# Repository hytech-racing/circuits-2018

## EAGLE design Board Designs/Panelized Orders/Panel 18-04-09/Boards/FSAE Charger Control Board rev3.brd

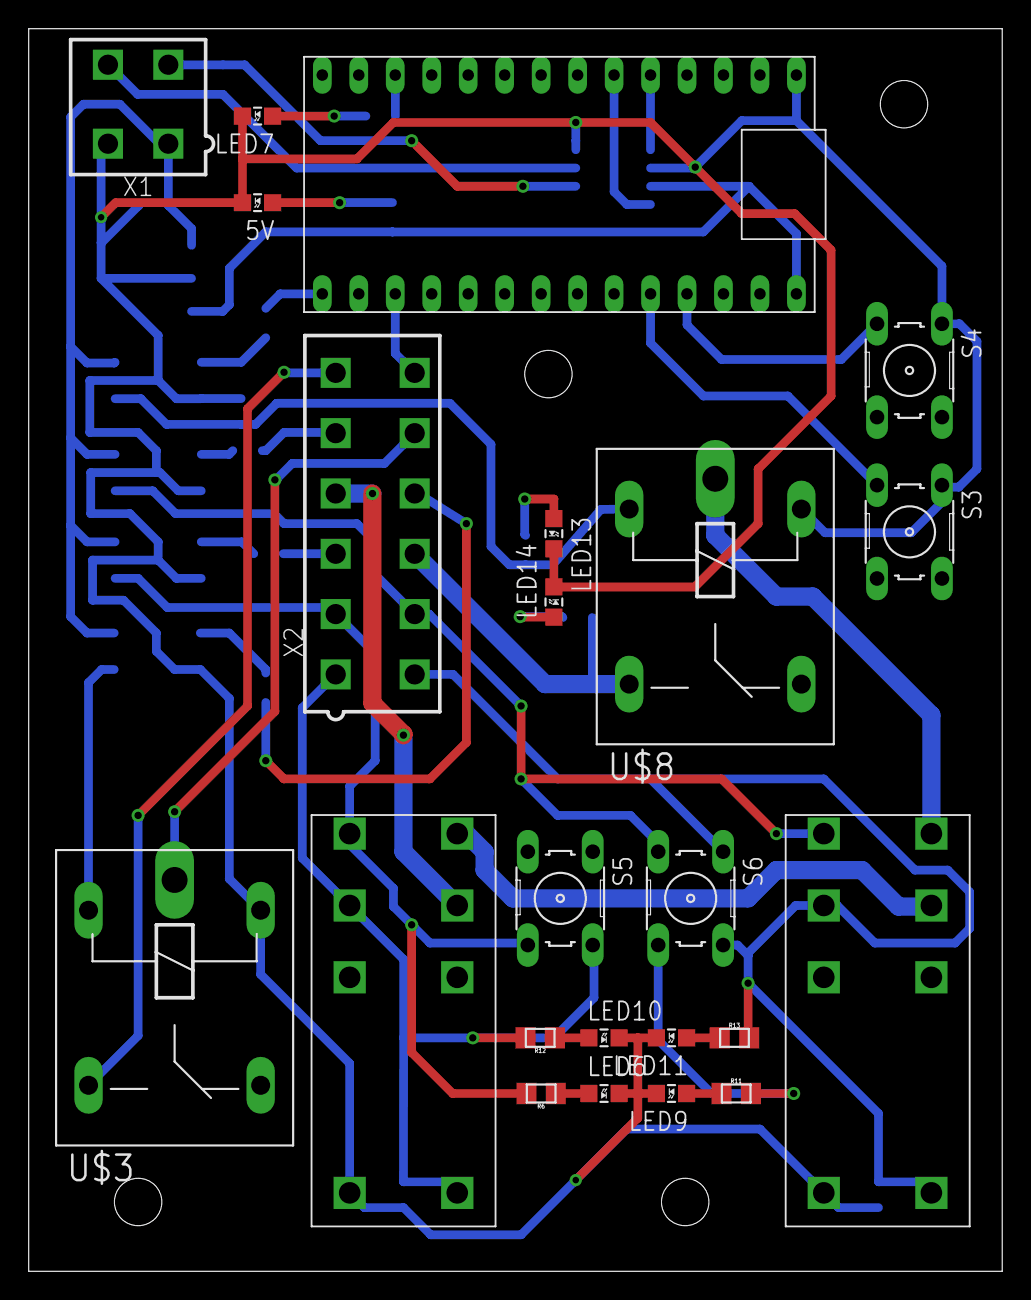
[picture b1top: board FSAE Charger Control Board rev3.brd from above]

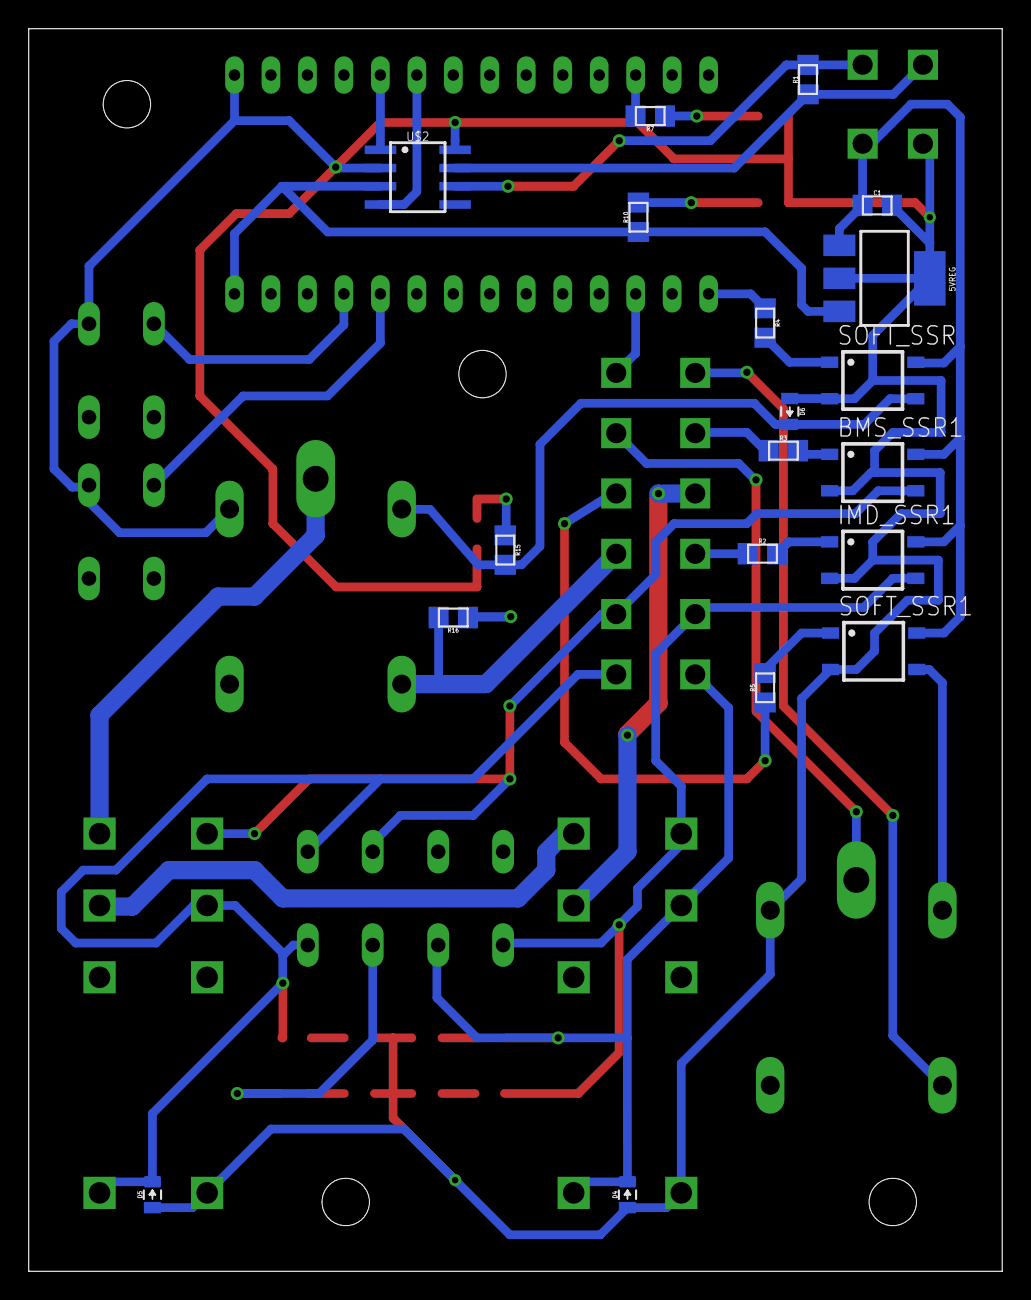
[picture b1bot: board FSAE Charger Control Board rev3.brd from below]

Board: 2 copper layers, 67.8 x 86.5 mm, 42 parts (19 on the bottom side), 39 nets.

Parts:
5V: LED-805
5VREG: SOT223
BMS_SSR1: CPC1002N; SOP04
C1: .22uF; 0805
D4, D5, D6: DIODE0805; 0805_D
IMD_SSR1: CPC1002N; SOP04
LED6, LED7, LED9, LED10, LED11, LED13, LED14: LED-805
R1: 120; 0805
R2, R3, R4, R5, R6, R7, R10, R11, R12, R13, R15, R16: 0805
S3, S4, S5, S6: B3F-10XX
SOFT_SSR, SOFT_SSR1: CPC1002N; SOP04
U$1: TEENSY_3.2_SIMPLE
U$2: MCP2551; SOIC-08
U$3, U$8: G5LE; ZF112
U$6, U$7: G2RL-2-DC12; G2RL-2
X1: CONNECTOR-4; MINIFIT_5566-4
X2: CONNECTOR-12; MINIFIT_5566-12

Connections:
+5V: 5VREG.3, R10.1, U$1.VIN, U$2.3
+12V: 5VREG.1, BMS_SSR1.4, C1.1, IMD_SSR1.4, SOFT_SSR.4, SOFT_SSR1.4, X1.1
BMS_12V: BMS_SSR1.3, R11.2, S6.3, S6.4, U$7.4, X2.8
BMS_INRLK: R5.1, X2.10
BMS_OK: D5.C, R13.2, S6.1, S6.2, U$7.3, U$7.COIL-, X2.7
BTN_X: S4.3, U$1.A9
BTN_Y: S3.3, U$1.A8
CANH: R1.1, U$2.7, X1.4
CANL: R1.2, U$2.6, X1.3
CANRX: U$1.D4(CANRX), U$2.4
CANTX: U$1.D3(CANTX), U$2.1
GND: 5V.C, 5VREG.2, 5VREG.4, BMS_SSR1.2, C1.2, D4.A, D5.A, D6.A, IMD_SSR1.2, LED6.C, LED7.C, LED9.C, LED10.C, LED11.C, LED13.C, LED14.C, S3.1, S4.1, SOFT_SSR.2, SOFT_SSR1.2, U$1.GND, U$2.2, U$2.8, U$3.1, U$6.COIL+, U$7.COIL+, U$8.1, X1.2
GPIO: U$1.A1, X2.12
IMD_12V: IMD_SSR1.3, R6.2, S5.3, S5.4, U$6.4, X2.2
IMD_OK: D4.C, R12.2, S5.1, S5.2, U$6.3, U$6.COIL-, X2.1
unnamed: SOFT_SSR1.3, U$3.2
unnamed: LED7.A, R7.1
unnamed: 5V.A, R10.2
unnamed: IMD_SSR1.1, R2.2
unnamed: U$3.S, X2.6
unnamed: LED6.A, R6.1
unnamed: LED9.A, R11.1
unnamed: LED10.A, R12.1
unnamed: U$3.P, X2.11
unnamed: R7.2, U$1.D10(TX2)
unnamed: BMS_SSR1.1, R3.2
unnamed: LED11.A, R13.1
unnamed: LED14.A, R16.1
unnamed: LED13.A, R15.1
unnamed: R2.1, X2.3
unnamed: R3.1, X2.5
unnamed: R5.2, SOFT_SSR1.1
unnamed: R4.1, U$1.D13
SHUTDOWN_IN: U$6.6, X2.4
SHUTDOWN_IN_A: U$6.5, U$7.6
SHUTDOWN_IN_B: U$7.5, U$8.P
SHUTDOWN_OUT: R16.2, U$8.S, X2.9
SW_KILL: R4.2, SOFT_SSR.1
SW_KILL_RELAY: D6.C, R15.2, SOFT_SSR.3, U$8.2

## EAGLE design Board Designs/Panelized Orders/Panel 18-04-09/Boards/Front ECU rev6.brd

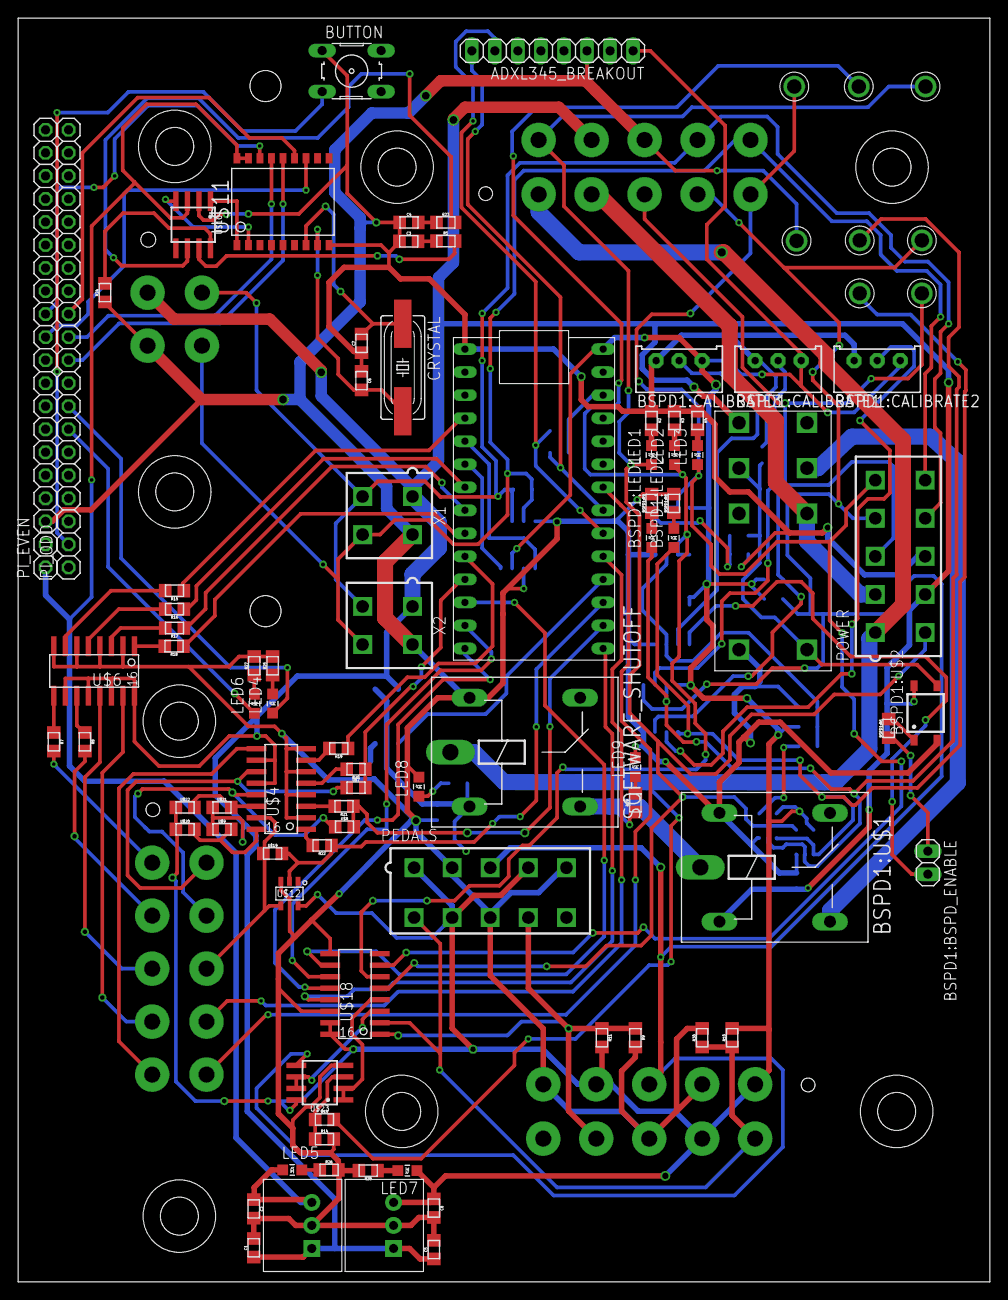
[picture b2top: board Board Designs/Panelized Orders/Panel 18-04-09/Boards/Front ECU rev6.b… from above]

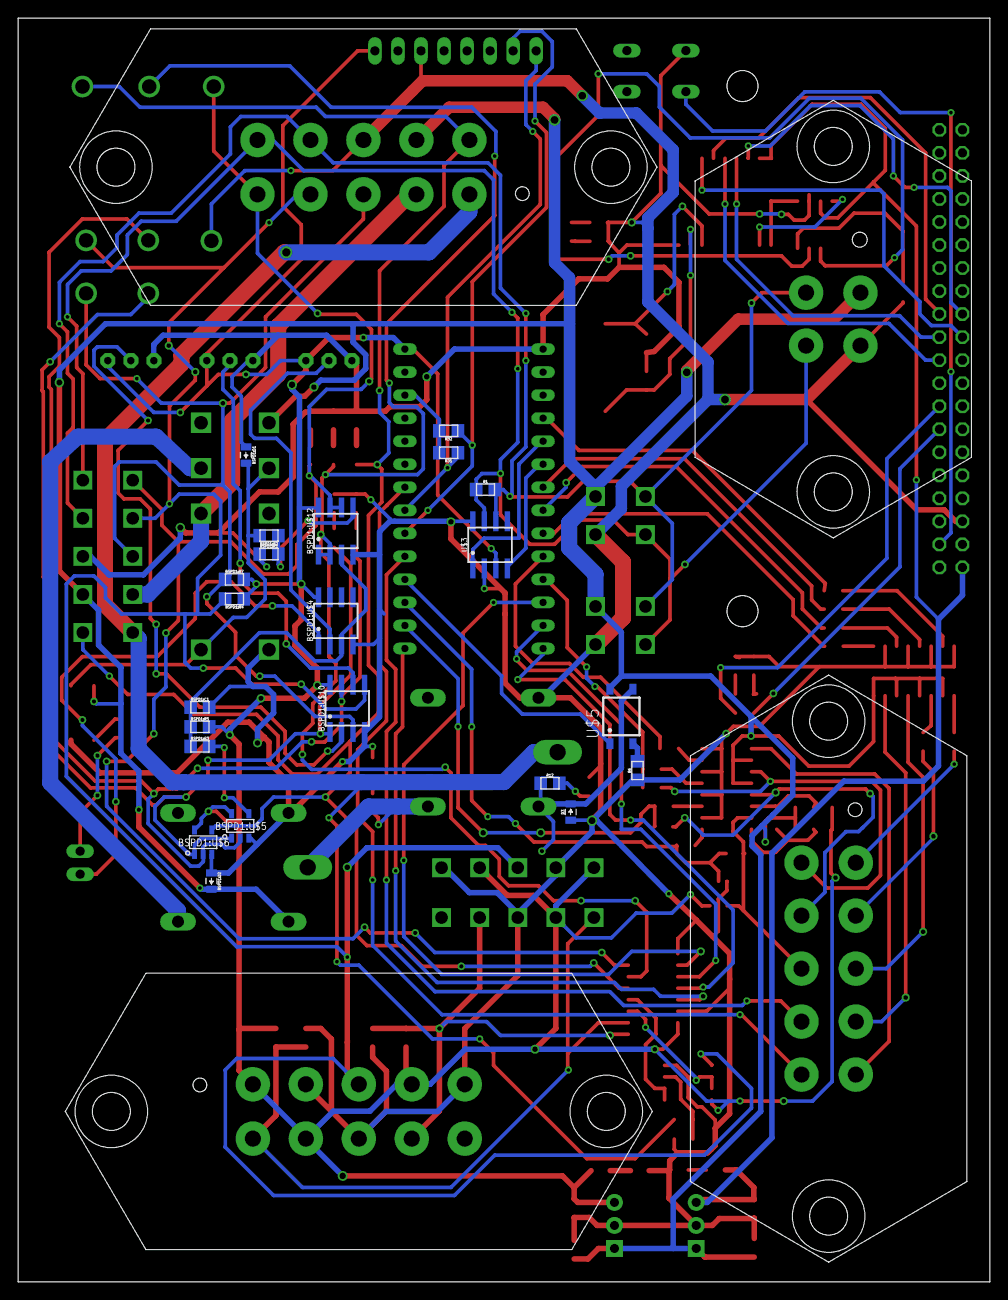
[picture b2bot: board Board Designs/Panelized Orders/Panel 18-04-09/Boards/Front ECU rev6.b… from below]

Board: 2 copper layers, 107.2 x 139.4 mm, 117 parts (26 on the bottom side), 102 nets.

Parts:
ADXL345_BREAKOUT: 1X08
BSPD1:BSPD_ENABLE: JUMPER; 1X02
BSPD1:C1: .47u; 0805
BSPD1:CALIBRATE1, BSPD1:CALIBRATE2, BSPD1:CALIBRATE3: TRIMPOT_3296
BSPD1:D1, BSPD1:D2: DIODE0805; 0805_D
BSPD1:LED1: RED; LED-805
BSPD1:LED2: YELLOW; LED-805
BSPD1:R1: 12k; 0805
BSPD1:R2: 43k; 0805
BSPD1:R3: 330; 0805
BSPD1:R4, BSPD1:R7: 10k; 0805
BSPD1:R5: 680k; 0805
BSPD1:R6: 680; 0805
BSPD1:R8, BSPD1:R9: 270; 0805
BSPD1:U$1: G5LE; ZF112
BSPD1:U$2: CPC1002N; SOP04
BSPD1:U$3: JW2SN-DC12V; JW2SN
BSPD1:U$4, BSPD1:U$10: MCP6542SOIC; SOIC-08
BSPD1:U$5: SN74AHC1G09; SOT-23-5
BSPD1:U$6: SN74LVC1G08; SOT-23-5
BSPD1:U$11, BSPD1:U$13: TEST_POINT
BSPD1:U$12: MCP6002SOIC; SOIC-08
BUTTON: B3F-10XX
C1, C2, C5, C8: 10uF; 0805
C3, C4: 560pF; 0805
C6, C7: 22pF; 0805
CRYSTAL: 16MHz; HC49UP
D3: DIODE0805; 0805_D
IC2, IC3: OKI-78SR
LED1, LED6, LED8, LED9: RED; LED-805
LED2: YELLOW; LED-805
LED3, LED4: GREEN; LED-805
LED5, LED7: PURPLE; LED-805
PEDALS: MINIFIT_5566-10
PI_EVEN: 1X20
PI_ODD: 1X20
POWER: MINIFIT_5566-10
R1: 120; 0805
R2, R3, R15, R16, R17, R18, R19, R20, R21, R22, R27: 270; 0805
R4, R25, R26, R28: 200; 0805
R5, R23: 100; 0805
R6: 330; 0805
R7, R8: 0; 0805
R9, R10, R11, R30: 10k; 0805
R12, R29: 1.2K; 0805
R13: 43k; 0805
R14: 12k; 0805
R24, R31, R32: 4.7k; 0805
SOFTWARE_SHUTOFF: G5LE; ZF112
U$1: TEENSY_3.2_SIMPLE
U$2, U$13, U$14, U$15, U$16, U$17: TEST_POINT
U$3, U$10: MCP2551; SOIC-08
U$4, U$6: TLP291-4; SOIC-16
U$5: CPC1002N; SOP04
U$7, U$8, U$9, U$19, U$20, U$21, U$22: JUMPER; 0805
U$11: MCP2515SMD; SOIC-18W
U$12: SN74LV1T34; SOT-23-5
U$18: MCP3208SOIC; SOIC-16
U$23: MCP6002SOIC; SOIC-08
X1, X2: CONNECTOR-4; MINIFIT_5566-4
X3: CONNECTOR-4MX150L_VERTICAL-4; MX150L_VERTICAL-4
X4, X5, X6: CONNECTOR-10MX150L_VERTICAL-10; MX150L_VERTICAL-10

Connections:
3.3V+: R31.2, R32.2, U$1.3.3V
+5V: ADXL345_BREAKOUT.1, BSPD1:CALIBRATE1.1, BSPD1:CALIBRATE2.1, BSPD1:CALIBRATE3.1, BSPD1:R4.1, BSPD1:R5.2, BSPD1:R7.2, BSPD1:U$4.8, BSPD1:U$5.5, BSPD1:U$6.5, BSPD1:U$10.8, BSPD1:U$12.8, C8.1, IC3.3, LED7.A, PEDALS.1, PEDALS.4, PEDALS.7, R10.2, R11.2, U$1.VIN, U$3.3, U$12.5, U$18.15, U$18.16, U$20.1, U$22.1, U$23.8, X4.1, X4.4, X4.7
+5V/1: C2.1, IC2.3, LED5.A, PI_EVEN.1, U$10.3, U$11.17, U$11.18
+12V: BSPD1:D2.C, BSPD1:U$1.2, BSPD1:U$2.4, BSPD1:U$3.4, C1.1, C5.1, IC2.1, IC3.1, POWER.7, U$4.10, U$4.12, U$5.4, U$6.10, U$6.12, U$6.14, U$6.16, U$9.1, U$21.1, X1.1, X2.1, X3.1, X5.7
BSPD1:N$1: BSPD1:D1.C, BSPD1:R2.2, BSPD1:U$2.3, BSPD1:U$3.3, BSPD1:U$3.COIL-
BSPD1:N$2: BSPD1:R3.2, BSPD1:U$5.4
BSPD1:N$3: BSPD1:R6.2, BSPD1:U$2.1
BSPD1:N$4: BSPD1:BSPD_ENABLE.1, BSPD1:R6.1
BSPD1:N$5: BSPD1:CALIBRATE2.2, BSPD1:U$10.2
BSPD1:N$6: BSPD1:CALIBRATE1.2, BSPD1:U$10.6
BSPD1:N$7: BSPD1:CALIBRATE3.2, BSPD1:U$4.2
BSPD1:N$8: BSPD1:BSPD_ENABLE.2, BSPD1:U$4.1
BSPD1:N$9: BSPD1:R1.2, BSPD1:R2.1, BSPD1:U$12.5
BSPD1:N$13: BSPD1:C1.1, BSPD1:R3.1, BSPD1:R5.1, BSPD1:U$4.3, BSPD1:U$12.3
BSPD1:N$14: BSPD1:LED2.C, BSPD1:R8.1
BSPD1:N$15: BSPD1:LED1.C, BSPD1:R9.1
BSPD1:N$16: BSPD1:LED1.A, BSPD1:U$5.2, BSPD1:U$6.2, BSPD1:U$10.7, BSPD1:U$11.P$1
BSPD1:N$17: BSPD1:LED2.A, BSPD1:U$5.1, BSPD1:U$6.1, BSPD1:U$10.1, BSPD1:U$13.P$1
BSPD1:SHUTDOWN_C: BSPD1:U$1.S, BSPD1:U$3.6
BUT: BUTTON.3, PI_ODD.2
CAN-H: R5.2, U$10.7
CAN-L: R23.2, U$10.6
CANH: POWER.10, R1.1, U$3.7, X1.4, X2.4, X3.4, X5.10
CANL: POWER.9, R1.2, U$3.6, X1.3, X2.3, X3.3, X5.9
CS: PI_EVEN.12, U$11.16
CS_MCP3208: U$1.D10(TX2), U$18.10
DASH_CTRL1: R15.1, U$1.D2
DASH_CTRL2: R16.1, U$1.D5
DASH_CTRL3: R17.1, U$1.D6
DASH_CTRL4: R18.1, U$1.D7(RX3)
DASH_CTRL5: R19.1, U$1.D8(TX3)
DASH_CTRL6: R20.1, U$1.D9(RX2), U$7.2
DASH_CTRL7: R21.1, U$1.A0, U$8.2
DASH_CTRL8: R22.1, U$1.A1, U$12.2, U$19.2
DASH_CTRL9: U$1.A3, X6.9
DASH_CTRL10: U$1.A6, X6.10
DASH_IO1: R7.2, X6.1
DASH_IO2: R8.2, X6.2
DASH_IO3: U$6.13, X6.3
DASH_IO4: U$6.15, X6.4
DASH_IO5: U$4.9, X6.5
DASH_IO6: U$4.11, U$7.1, X6.6
DASH_IO7: U$4.13, U$8.1, X6.7
DASH_IO8: U$4.15, U$12.4, U$19.1, X6.8
GND: ADXL345_BREAKOUT.3, BSPD1:C1.2, BSPD1:CALIBRATE1.3, BSPD1:CALIBRATE2.3, BSPD1:CALIBRATE3.3, BSPD1:D1.A, BSPD1:D2.A, BSPD1:R1.1, BSPD1:R8.2, BSPD1:R9.2, BSPD1:U$1.1, BSPD1:U$2.2, BSPD1:U$3.COIL+, BSPD1:U$4.4, BSPD1:U$5.3, BSPD1:U$6.3, BSPD1:U$10.4, BSPD1:U$12.4, BUTTON.1, C1.2, C2.2, C3.1, C4.1, C5.2, C6.1, C7.1, C8.2, D3.A, IC2.2, IC3.2, LED8.C, LED9.C, PEDALS.2, PEDALS.5, PEDALS.8, PI_EVEN.3, POWER.8, R2.1, R3.1, R4.1, R6.1, R9.2, R14.2, R24.1, R25.2, R26.2, R27.2, R28.2, R30.2, SOFTWARE_SHUTOFF.1, U$1.GND, U$2.P$1, U$3.2, U$3.8, U$4.2, U$4.4, U$4.6, U$4.8, U$6.2, U$6.4, U$6.6, U$6.8, U$10.2, U$11.9, U$12.3, U$18.9, U$18.14, U$23.4, X1.2, X2.2, X3.2, X4.2, X4.5, X4.8, X5.8
INT: PI_EVEN.11, U$11.12
LED1: LED4.A, PI_ODD.8
LED2: LED6.A, PI_ODD.7
MISO: PI_ODD.11, U$11.15
MISO_TEENSY: U$1.D12, U$18.12
MOSI: PI_ODD.10, U$11.14
MOSI_TEENSY: U$1.D11, U$18.11
unnamed: R7.1, U$6.9
unnamed: U$1.D4(CANRX), U$3.4
unnamed: R8.1, U$6.11
unnamed: U$4.16, U$9.2, U$20.2
unnamed: U$1.D3(CANTX), U$3.1
unnamed: U$4.14, U$21.2, U$22.2
unnamed: R13.1, R14.1, U$23.3
unnamed: LED8.A, R12.2
unnamed: LED9.A, R29.2
unnamed: D3.C, R12.1, SOFTWARE_SHUTOFF.2, U$5.3
unnamed: LED1.C, R2.2
unnamed: LED2.C, R3.2
unnamed: LED3.C, R4.2
unnamed: R15.2, U$6.7
unnamed: R6.2, U$5.2
unnamed: R16.2, U$6.5
unnamed: R21.2, U$4.3
unnamed: R17.2, U$6.3
unnamed: R18.2, U$6.1
unnamed: R19.2, U$4.7
unnamed: R20.2, U$4.5
unnamed: R22.2, U$4.1
unnamed: U$10.1, U$11.1
unnamed: U$10.4, U$11.2
unnamed: C6.2, CRYSTAL.2, U$11.8
unnamed: R24.2, U$10.8
unnamed: C7.2, CRYSTAL.1, U$11.7
unnamed: C3.2, R5.1
unnamed: C4.2, R23.1
unnamed: LED4.C, R25.1
unnamed: LED5.C, R26.1
unnamed: LED6.C, R27.1
unnamed: LED7.C, R28.1
READ_BRAKE: U$18.3, U$23.6, U$23.7
READ_CHARGE: BSPD1:U$12.1, BSPD1:U$12.2, LED2.A, U$16.P$1, U$18.6
READ_FAULT: BSPD1:U$12.6, BSPD1:U$12.7, LED3.A, POWER.5, U$15.P$1, U$18.7, X5.5
READ_SWITCH: BSPD1:U$6.4, LED1.A, POWER.6, U$17.P$1, U$18.5, X5.6
READ_UPSTREAM_SHUTDOWN: U$18.4, U$23.1, U$23.2
SCK: PI_ODD.12, U$11.13
SCK_TEENSY: U$1.D13, U$18.13
SCL: ADXL345_BREAKOUT.8, R31.1, U$1.A5
SDA: ADXL345_BREAKOUT.7, R32.1, U$1.A4
SHUTDOWN_A: POWER.1, R13.2, SOFTWARE_SHUTOFF.P, X5.1
SHUTDOWN_B: BSPD1:U$1.P, R29.1, SOFTWARE_SHUTOFF.S
SHUTDOWN_D: BSPD1:U$3.7, POWER.2, X5.2
SHUTDOWN_RELAY_CTRL: U$1.A2, U$5.1
SIGNAL_ACCEL1: PEDALS.9, R9.1, R11.1, U$18.1, X4.9
SIGNAL_ACCEL2: PEDALS.6, R10.1, R30.1, U$18.2, X4.6
SIGNAL_BRAKE: BSPD1:R4.2, BSPD1:U$10.5, PEDALS.3, POWER.4, U$13.P$1, U$23.5, X4.3, X5.4
SIGNAL_CURRENT: BSPD1:R7.1, BSPD1:U$10.3, POWER.3, U$14.P$1, X5.3

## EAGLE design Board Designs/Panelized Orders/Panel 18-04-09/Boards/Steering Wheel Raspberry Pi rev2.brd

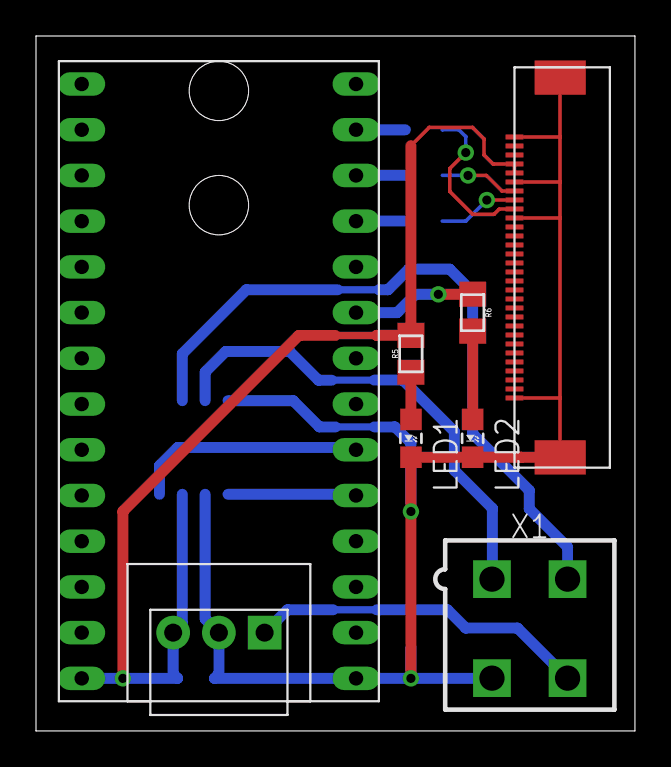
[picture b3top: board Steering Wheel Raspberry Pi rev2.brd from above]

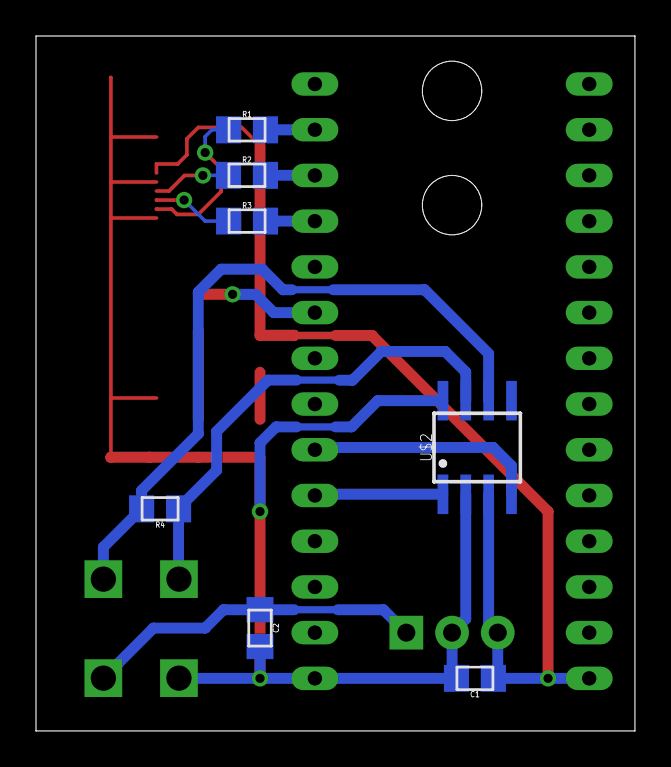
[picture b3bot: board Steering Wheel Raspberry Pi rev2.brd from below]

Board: 2 copper layers, 33.3 x 38.6 mm, 15 parts (7 on the bottom side), 16 nets.

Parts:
C1: 0.1uF; 0805
C2: 0.33uF; 0805
IC1: TO-220
LED1, LED2: LED-805
R1, R2, R3, R5, R6: 0805
R4: 120; 0805
U$1: TEENSY_3.2_SIMPLE
U$2: MCP2551; SOIC-08
U$3: FFC-30P-0.5MM
X1: CONNECTOR-4; MINIFIT_5566-4

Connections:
+5V: C1.1, IC1.3, R5.2, U$1.VIN, U$2.3, U$3.26, U$3.27
+12V: C2.1, IC1.1, X1.4
CANH: R4.1, U$2.7, X1.1
CANL: R4.2, U$2.6, X1.2
CANRX: U$1.D4(CANRX), U$2.4
CANTX: U$1.D3(CANTX), U$2.1
GND: C1.2, C2.2, IC1.2, LED1.C, LED2.C, U$1.GND, U$2.2, U$2.8, U$3.1, U$3.21, U$3.25, U$3.30, U$3.PAD@0, U$3.PAD@1, X1.3
unnamed: LED1.A, R5.1
unnamed: R6.1, U$1.D7(RX3)
unnamed: LED2.A, R6.2
RESET: R1.1, U$3.22
RX0: R3.1, U$3.23
TX0: R2.1, U$3.24
UC_RST: R1.2, U$1.D11
UC_RX: R3.2, U$1.D9(RX2)
UC_TX: R2.2, U$1.D10(TX2)

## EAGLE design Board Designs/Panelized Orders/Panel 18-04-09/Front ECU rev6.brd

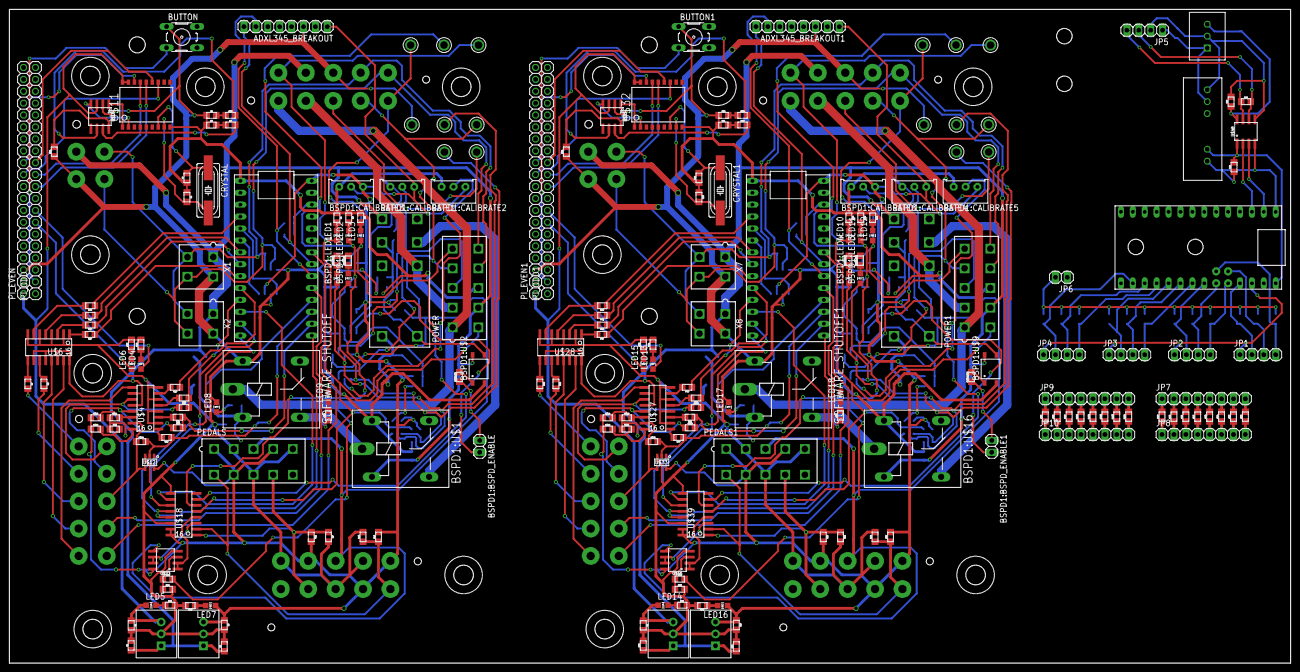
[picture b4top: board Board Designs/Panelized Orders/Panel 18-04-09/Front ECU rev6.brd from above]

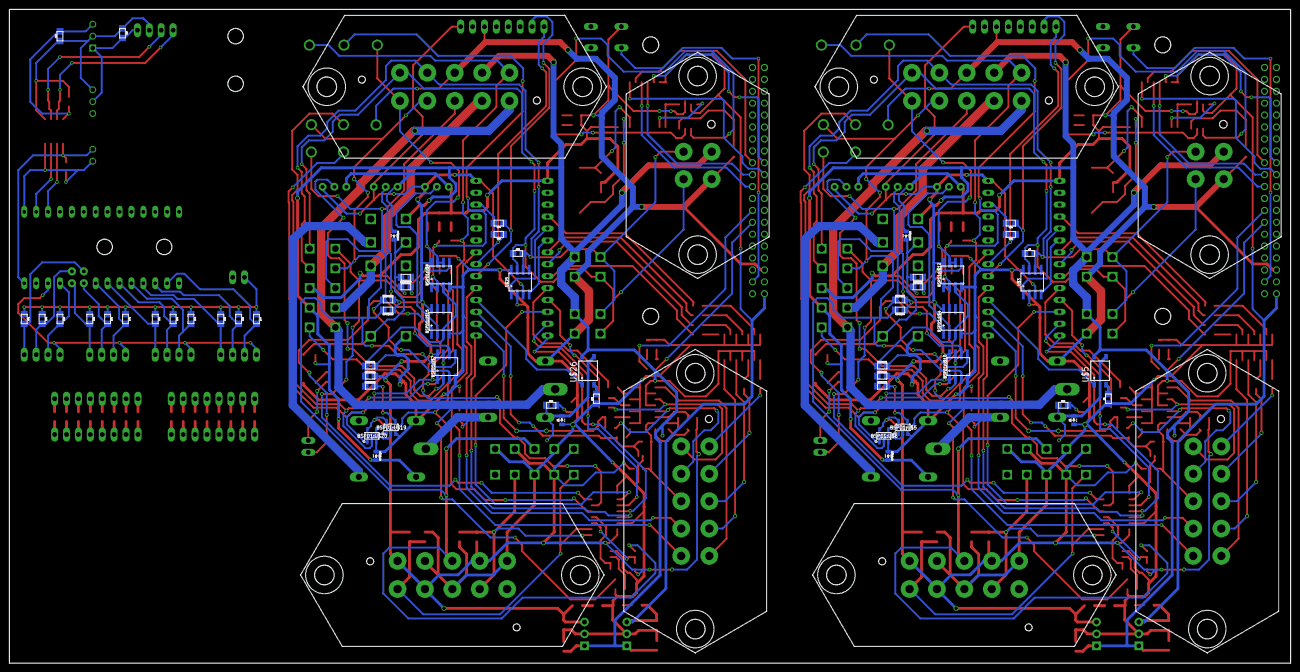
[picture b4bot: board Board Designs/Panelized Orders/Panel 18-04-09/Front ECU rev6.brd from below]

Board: 2 copper layers, 273.3 x 139.4 mm, 281 parts (66 on the bottom side), 259 nets.

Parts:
ADXL345_BREAKOUT, ADXL345_BREAKOUT1: 1X08
BSPD1:BSPD_ENABLE, BSPD1:BSPD_ENABLE1: JUMPER; 1X02
BSPD1:C1, BSPD1:C2: .47u; 0805
BSPD1:CALIBRATE1, BSPD1:CALIBRATE2, BSPD1:CALIBRATE3, BSPD1:CALIBRATE4, BSPD1:CALIBRATE5, BSPD1:CALIBRATE6: TRIMPOT_3296
BSPD1:D1, BSPD1:D2, BSPD1:D3, BSPD1:D4: DIODE0805; 0805_D
BSPD1:LED1, BSPD1:LED4: RED; LED-805
BSPD1:LED2, BSPD1:LED3: YELLOW; LED-805
BSPD1:R1, BSPD1:R17: 12k; 0805
BSPD1:R2, BSPD1:R18: 43k; 0805
BSPD1:R3, BSPD1:R10: 330; 0805
BSPD1:R4, BSPD1:R7, BSPD1:R13, BSPD1:R14: 10k; 0805
BSPD1:R5, BSPD1:R11: 680k; 0805
BSPD1:R6, BSPD1:R12: 680; 0805
BSPD1:R8, BSPD1:R9, BSPD1:R15, BSPD1:R16: 270; 0805
BSPD1:U$1, BSPD1:U$16: G5LE; ZF112
BSPD1:U$2, BSPD1:U$9: CPC1002N; SOP04
BSPD1:U$3, BSPD1:U$14: JW2SN-DC12V; JW2SN
BSPD1:U$4, BSPD1:U$7, BSPD1:U$10, BSPD1:U$15: MCP6542SOIC; SOIC-08
BSPD1:U$5, BSPD1:U$19: SN74AHC1G09; SOT-23-5
BSPD1:U$6, BSPD1:U$20: SN74LVC1G08; SOT-23-5
BSPD1:U$8, BSPD1:U$12: MCP6002SOIC; SOIC-08
BSPD1:U$11, BSPD1:U$13, BSPD1:U$17, BSPD1:U$18: TEST_POINT
BUTTON, BUTTON1: B3F-10XX
C1, C2, C5, C8, C9, C10, C15, C16: 10uF; 0805
C3, C4, C11, C12: 560pF; 0805
C6, C7, C13, C14: 22pF; 0805
C17, C18, C20: 0.1u; 0805
C19: 0.33u; 0805
CRYSTAL, CRYSTAL1: 16MHz; HC49UP
D1, D3: DIODE0805; 0805_D
IC1, IC2, IC3, IC4: OKI-78SR
IC5: TO-220-SPACED
JP1, JP2, JP3, JP4, JP5: 1X04
JP6: M02; 1X02
JP7, JP8, JP9, JP10: 1X08
LED1, LED6, LED8, LED9, LED10, LED15, LED17, LED18: RED; LED-805
LED2, LED11: YELLOW; LED-805
LED3, LED4, LED12, LED13: GREEN; LED-805
LED5, LED7, LED14, LED16: PURPLE; LED-805
PEDALS, PEDALS1: MINIFIT_5566-10
PI_EVEN, PI_EVEN1: 1X20
PI_ODD, PI_ODD1: 1X20
POWER, POWER1: MINIFIT_5566-10
R1, R33, R67: 120; 0805
R2, R3, R15, R16, R17, R18, R19, R20, R21, R22, R27, R34, R35, R40, R41, R42, R43, R44, R45, R46, R47, R53: 270; 0805
R4, R25, R26, R28, R36, R51, R52, R54: 200; 0805
R5, R23, R48, R49: 100; 0805
R6, R37: 330; 0805
R7, R8, R55, R56: 0; 0805
R9, R10, R11, R30, R57, R58, R61, R62: 10k; 0805
R12, R29, R59, R60: 1.2K; 0805
R13, R38: 43k; 0805
R14, R39: 12k; 0805
R24, R31, R32, R50, R63, R64: 4.7k; 0805
R65, R66, R68, R69, R70, R71, R72, R73, R74, R75, R76, R77, R89, R90, R91, R92, R93, R94, R95, R96, R97, R98, R99, R100, R101, R102, R103, R104: 0805
SOFTWARE_SHUTOFF, SOFTWARE_SHUTOFF1: G5LE; ZF112
U$1, U$24: TEENSY_3.2_SIMPLE
U$2, U$13, U$14, U$15, U$16, U$17, U$34, U$35, U$36, U$37, U$38, U$45: TEST_POINT
U$3, U$10, U$25, U$31: MCP2551; SOIC-08
U$4, U$6, U$27, U$28: TLP291-4; SOIC-16
U$5, U$26: CPC1002N; SOP04
U$7, U$8, U$9, U$19, U$20, U$21, U$22, U$29, U$30, U$40, U$41, U$42, U$43, U$44: JUMPER; 0805
U$11, U$32: MCP2515SMD; SOIC-18W
U$12, U$33: SN74LV1T34; SOT-23-5
U$18, U$39: MCP3208SOIC; SOIC-16
U$23, U$46: MCP6002SOIC; SOIC-08
U$47: TEENSY_3.2_12ANALOG
U$48: ISO1050CAN; SOIC-08
U$49: NCS1S1205SC-12V-5VCONVERTER; DCDC-CONVERTER
X1, X2, X7, X8: CONNECTOR-4; MINIFIT_5566-4
X3, X9: CONNECTOR-4MX150L_VERTICAL-4; MX150L_VERTICAL-4
X4, X5, X6, X10, X11, X12: CONNECTOR-10MX150L_VERTICAL-10; MX150L_VERTICAL-10

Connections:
3.3V: JP1.1, JP2.1, JP3.1, JP4.1, U$47.3.3V
3.3V+: R31.2, R32.2, U$1.3.3V
3.3V+1: R63.2, R64.2, U$24.3.3V
+5V: ADXL345_BREAKOUT.1, BSPD1:CALIBRATE1.1, BSPD1:CALIBRATE2.1, BSPD1:CALIBRATE3.1, BSPD1:R4.1, BSPD1:R5.2, BSPD1:R7.2, BSPD1:U$4.8, BSPD1:U$5.5, BSPD1:U$6.5, BSPD1:U$10.8, BSPD1:U$12.8, C8.1, IC3.3, LED7.A, PEDALS.1, PEDALS.4, PEDALS.7, R10.2, R11.2, U$1.VIN, U$3.3, U$12.5, U$18.15, U$18.16, U$20.1, U$22.1, U$23.8, X4.1, X4.4, X4.7
+5V1: ADXL345_BREAKOUT1.1, BSPD1:CALIBRATE4.1, BSPD1:CALIBRATE5.1, BSPD1:CALIBRATE6.1, BSPD1:R11.2, BSPD1:R13.1, BSPD1:R14.2, BSPD1:U$7.8, BSPD1:U$8.8, BSPD1:U$15.8, BSPD1:U$19.5, BSPD1:U$20.5, C16.1, IC4.3, LED16.A, PEDALS1.1, PEDALS1.4, PEDALS1.7, R57.2, R58.2, U$24.VIN, U$25.3, U$33.5, U$39.15, U$39.16, U$42.1, U$44.1, U$46.8, X10.1, X10.4, X10.7
+5V/1: C2.1, IC2.3, LED5.A, PI_EVEN.1, U$10.3, U$11.17, U$11.18
+5V/2: C9.1, IC1.3, LED14.A, PI_EVEN1.1, U$31.3, U$32.17, U$32.18
+12V: BSPD1:D2.C, BSPD1:U$1.2, BSPD1:U$2.4, BSPD1:U$3.4, C1.1, C5.1, IC2.1, IC3.1, POWER.7, U$4.10, U$4.12, U$5.4, U$6.10, U$6.12, U$6.14, U$6.16, U$9.1, U$21.1, X1.1, X2.1, X3.1, X5.7
+12V1: BSPD1:D4.C, BSPD1:U$9.4, BSPD1:U$14.4, BSPD1:U$16.2, C10.1, C15.1, IC1.1, IC4.1, POWER1.7, U$26.4, U$27.10, U$27.12, U$28.10, U$28.12, U$28.14, U$28.16, U$41.1, U$43.1, X7.1, X8.1, X9.1, X11.7
BSPD1:N$1: BSPD1:D1.C, BSPD1:R2.2, BSPD1:U$2.3, BSPD1:U$3.3, BSPD1:U$3.COIL-
BSPD1:N$2: BSPD1:R3.2, BSPD1:U$5.4
BSPD1:N$3: BSPD1:R6.2, BSPD1:U$2.1
BSPD1:N$4: BSPD1:BSPD_ENABLE.1, BSPD1:R6.1
BSPD1:N$5: BSPD1:CALIBRATE2.2, BSPD1:U$10.2
BSPD1:N$6: BSPD1:CALIBRATE1.2, BSPD1:U$10.6
BSPD1:N$7: BSPD1:CALIBRATE3.2, BSPD1:U$4.2
BSPD1:N$8: BSPD1:BSPD_ENABLE.2, BSPD1:U$4.1
BSPD1:N$9: BSPD1:R1.2, BSPD1:R2.1, BSPD1:U$12.5
BSPD1:N$10: BSPD1:C2.1, BSPD1:R10.1, BSPD1:R11.1, BSPD1:U$8.3, BSPD1:U$15.3
BSPD1:N$11: BSPD1:CALIBRATE6.2, BSPD1:U$15.2
BSPD1:N$12: BSPD1:D3.C, BSPD1:R18.2, BSPD1:U$9.3, BSPD1:U$14.3, BSPD1:U$14.COIL-
BSPD1:N$13: BSPD1:C1.1, BSPD1:R3.1, BSPD1:R5.1, BSPD1:U$4.3, BSPD1:U$12.3
BSPD1:N$14: BSPD1:LED2.C, BSPD1:R8.1
BSPD1:N$15: BSPD1:LED1.C, BSPD1:R9.1
BSPD1:N$16: BSPD1:LED1.A, BSPD1:U$5.2, BSPD1:U$6.2, BSPD1:U$10.7, BSPD1:U$11.P$1
BSPD1:N$17: BSPD1:LED2.A, BSPD1:U$5.1, BSPD1:U$6.1, BSPD1:U$10.1, BSPD1:U$13.P$1
BSPD1:N$18: BSPD1:R10.2, BSPD1:U$19.4
BSPD1:N$19: BSPD1:R12.2, BSPD1:U$9.1
BSPD1:N$20: BSPD1:LED4.C, BSPD1:R16.1
BSPD1:N$21: BSPD1:LED3.C, BSPD1:R15.1
BSPD1:N$22: BSPD1:LED4.A, BSPD1:U$7.7, BSPD1:U$17.P$1, BSPD1:U$19.2, BSPD1:U$20.2
BSPD1:N$23: BSPD1:LED3.A, BSPD1:U$7.1, BSPD1:U$18.P$1, BSPD1:U$19.1, BSPD1:U$20.1
BSPD1:N$24: BSPD1:BSPD_ENABLE1.1, BSPD1:R12.1
BSPD1:N$25: BSPD1:BSPD_ENABLE1.2, BSPD1:U$15.1
BSPD1:N$26: BSPD1:CALIBRATE5.2, BSPD1:U$7.2
BSPD1:N$27: BSPD1:CALIBRATE4.2, BSPD1:U$7.6
BSPD1:N$28: BSPD1:R17.2, BSPD1:R18.1, BSPD1:U$8.5
BSPD1:SHUTDOWN_C: BSPD1:U$1.S, BSPD1:U$3.6
BSPD1:SHUTDOWN_C1: BSPD1:U$14.6, BSPD1:U$16.S
BUT: BUTTON.3, PI_ODD.2
BUT1: BUTTON1.3, PI_ODD1.2
CAN-H: R5.2, U$10.7
CAN-H1: R48.2, U$31.7
CAN-L: R23.2, U$10.6
CAN-L1: R49.2, U$31.6
CANH: POWER.10, R1.1, U$3.7, X1.4, X2.4, X3.4, X5.10
CANH1: POWER1.10, R33.1, U$25.7, X7.4, X8.4, X9.4, X11.10
CANL: POWER.9, R1.2, U$3.6, X1.3, X2.3, X3.3, X5.9
CANL1: POWER1.9, R33.2, U$25.6, X7.3, X8.3, X9.3, X11.9
CS: PI_EVEN.12, U$11.16
CS1: PI_EVEN1.12, U$32.16
CS_MCP1: U$24.D10(TX2), U$39.10
CS_MCP3208: U$1.D10(TX2), U$18.10
DASH_CTRL1: R15.1, U$1.D2
DASH_CTRL2: R16.1, U$1.D5
DASH_CTRL3: R17.1, U$1.D6
DASH_CTRL4: R18.1, U$1.D7(RX3)
DASH_CTRL5: R19.1, U$1.D8(TX3)
DASH_CTRL6: R20.1, U$1.D9(RX2), U$7.2
DASH_CTRL7: R21.1, U$1.A0, U$8.2
DASH_CTRL8: R22.1, U$1.A1, U$12.2, U$19.2
DASH_CTRL9: U$1.A3, X6.9
DASH_CTRL10: U$1.A6, X6.10
DASH_CTRL11: R41.1, U$24.D5
DASH_CTRL12: R42.1, U$24.D6
DASH_CTRL13: R43.1, U$24.D7(RX3)
DASH_CTRL14: R45.1, U$24.D9(RX2), U$29.2
DASH_CTRL15: R47.1, U$24.A1, U$33.2, U$40.2
DASH_CTRL16: U$24.A6, X12.10
DASH_CTRL17: R40.1, U$24.D2
DASH_CTRL18: R44.1, U$24.D8(TX3)
DASH_CTRL19: R46.1, U$24.A0, U$30.2
DASH_CTRL20: U$24.A3, X12.9
DASH_IO1: R7.2, X6.1
DASH_IO2: R8.2, X6.2
DASH_IO3: U$6.13, X6.3
DASH_IO4: U$6.15, X6.4
DASH_IO5: U$4.9, X6.5
DASH_IO6: U$4.11, U$7.1, X6.6
DASH_IO7: U$4.13, U$8.1, X6.7
DASH_IO8: U$4.15, U$12.4, U$19.1, X6.8
DASH_IO9: R55.2, X12.1
DASH_IO10: R56.2, X12.2
DASH_IO11: U$28.13, X12.3
DASH_IO12: U$28.15, X12.4
DASH_IO13: U$27.9, X12.5
DASH_IO14: U$27.11, U$29.1, X12.6
DASH_IO15: U$27.13, U$30.1, X12.7
DASH_IO16: U$27.15, U$33.4, U$40.1, X12.8
GND: ADXL345_BREAKOUT.3, BSPD1:C1.2, BSPD1:CALIBRATE1.3, BSPD1:CALIBRATE2.3, BSPD1:CALIBRATE3.3, BSPD1:D1.A, BSPD1:D2.A, BSPD1:R1.1, BSPD1:R8.2, BSPD1:R9.2, BSPD1:U$1.1, BSPD1:U$2.2, BSPD1:U$3.COIL+, BSPD1:U$4.4, BSPD1:U$5.3, BSPD1:U$6.3, BSPD1:U$10.4, BSPD1:U$12.4, BUTTON.1, C1.2, C2.2, C3.1, C4.1, C5.2, C6.1, C7.1, C8.2, D3.A, IC2.2, IC3.2, LED8.C, LED9.C, PEDALS.2, PEDALS.5, PEDALS.8, PI_EVEN.3, POWER.8, R2.1, R3.1, R4.1, R6.1, R9.2, R14.2, R24.1, R25.2, R26.2, R27.2, R28.2, R30.2, SOFTWARE_SHUTOFF.1, U$1.GND, U$2.P$1, U$3.2, U$3.8, U$4.2, U$4.4, U$4.6, U$4.8, U$6.2, U$6.4, U$6.6, U$6.8, U$10.2, U$11.9, U$12.3, U$18.9, U$18.14, U$23.4, X1.2, X2.2, X3.2, X4.2, X4.5, X4.8, X5.8
GND1: ADXL345_BREAKOUT1.3, BSPD1:C2.2, BSPD1:CALIBRATE4.3, BSPD1:CALIBRATE5.3, BSPD1:CALIBRATE6.3, BSPD1:D3.A, BSPD1:D4.A, BSPD1:R15.2, BSPD1:R16.2, BSPD1:R17.1, BSPD1:U$7.4, BSPD1:U$8.4, BSPD1:U$9.2, BSPD1:U$14.COIL+, BSPD1:U$15.4, BSPD1:U$16.1, BSPD1:U$19.3, BSPD1:U$20.3, BUTTON1.1, C9.2, C10.2, C11.1, C12.1, C13.1, C14.1, C15.2, C16.2, D1.A, IC1.2, IC4.2, LED17.C, LED18.C, PEDALS1.2, PEDALS1.5, PEDALS1.8, PI_EVEN1.3, POWER1.8, R34.1, R35.1, R36.1, R37.1, R39.2, R50.1, R51.2, R52.2, R53.2, R54.2, R61.2, R62.2, SOFTWARE_SHUTOFF1.1, U$24.GND, U$25.2, U$25.8, U$27.2, U$27.4, U$27.6, U$27.8, U$28.2, U$28.4, U$28.6, U$28.8, U$31.2, U$32.9, U$33.3, U$39.9, U$39.14, U$45.P$1, U$46.4, X7.2, X8.2, X9.2, X10.2, X10.5, X10.8, X11.8
INT: PI_EVEN.11, U$11.12
INT1: PI_EVEN1.11, U$32.12
LED1: LED4.A, PI_ODD.8
LED2: LED6.A, PI_ODD.7
LED3: LED15.A, PI_ODD1.7
LED4: LED13.A, PI_ODD1.8
MISO: PI_ODD.11, U$11.15
MISO1: PI_ODD1.11, U$32.15
MISO_TEENSY: U$1.D12, U$18.12
MISO_TEENSY1: U$24.D12, U$39.12
MOSI: PI_ODD.10, U$11.14
MOSI1: PI_ODD1.10, U$32.14
MOSI_TEENSY: U$1.D11, U$18.11
MOSI_TEENSY1: U$24.D11, U$39.11
unnamed: R7.1, U$6.9
unnamed: U$1.D4(CANRX), U$3.4
unnamed: R8.1, U$6.11
unnamed: U$4.16, U$9.2, U$20.2
unnamed: U$1.D3(CANTX), U$3.1
unnamed: U$4.14, U$21.2, U$22.2
unnamed: R13.1, R14.1, U$23.3
unnamed: LED8.A, R12.2
unnamed: LED9.A, R29.2
unnamed: U$24.D4(CANRX), U$25.4
unnamed: U$24.D3(CANTX), U$25.1
unnamed: D3.C, R12.1, SOFTWARE_SHUTOFF.2, U$5.3
unnamed: LED10.C, R34.2
unnamed: LED1.C, R2.2
unnamed: LED2.C, R3.2
unnamed: LED3.C, R4.2
unnamed: LED11.C, R35.2
unnamed: LED12.C, R36.2
unnamed: R15.2, U$6.7
unnamed: R37.2, U$26.2
unnamed: D1.C, R59.1, SOFTWARE_SHUTOFF1.2, U$26.3
unnamed: R6.2, U$5.2
unnamed: R40.2, U$28.7
unnamed: R16.2, U$6.5
unnamed: R41.2, U$28.5
unnamed: R42.2, U$28.3
unnamed: R21.2, U$4.3
unnamed: R17.2, U$6.3
unnamed: R18.2, U$6.1
unnamed: R43.2, U$28.1
unnamed: R19.2, U$4.7
unnamed: R20.2, U$4.5
unnamed: R44.2, U$27.7
unnamed: R45.2, U$27.5
unnamed: R22.2, U$4.1
unnamed: R46.2, U$27.3
unnamed: U$10.1, U$11.1
unnamed: R47.2, U$27.1
unnamed: U$10.4, U$11.2
unnamed: C6.2, CRYSTAL.2, U$11.8
unnamed: R24.2, U$10.8
unnamed: C7.2, CRYSTAL.1, U$11.7
unnamed: C3.2, R5.1
unnamed: U$31.1, U$32.1
unnamed: U$31.4, U$32.2
unnamed: C13.2, CRYSTAL1.2, U$32.8
unnamed: R50.2, U$31.8
unnamed: C14.2, CRYSTAL1.1, U$32.7
unnamed: C11.2, R48.1
unnamed: C4.2, R23.1
unnamed: C12.2, R49.1
unnamed: LED4.C, R25.1
unnamed: LED5.C, R26.1
unnamed: LED6.C, R27.1
unnamed: LED7.C, R28.1
unnamed: LED13.C, R51.1
unnamed: LED14.C, R52.1
unnamed: LED15.C, R53.1
unnamed: LED16.C, R54.1
unnamed: R55.1, U$28.9
unnamed: R56.1, U$28.11
unnamed: U$27.16, U$41.2, U$42.2
unnamed: U$27.14, U$43.2, U$44.2
unnamed: LED17.A, R59.2
unnamed: LED18.A, R60.2
unnamed: R38.1, R39.1, U$46.3
unnamed: JP3.3, R75.2, U$47.A4
unnamed: JP3.4, R76.2, U$47.A5
unnamed: C17.1, C20.2, IC5.3, U$48.8
unnamed: C17.2, C19.1, C20.1, IC5.2, JP5.2, U$48.5, U$49.-VIN
unnamed: C19.2, IC5.1, JP5.1, U$49.+VIN
unnamed: JP5.4, R67.1, U$48.7
unnamed: JP5.3, R67.2, U$48.6
unnamed: U$47.D0(RX1), U$48.3
unnamed: U$47.D1(TX1), U$48.2
unnamed: C18.2, U$47.VIN, U$48.1, U$49.+VOUT
unnamed: C18.1, U$47.GND, U$48.4, U$49.-VOUT
unnamed: JP2.4, R68.2, U$47.A8
unnamed: JP4.4, R69.2, U$47.A2
unnamed: JP7.1, R89.2
unnamed: JP8.8, R96.1
unnamed: JP8.7, R95.1
unnamed: JP7.2, R90.2
unnamed: JP8.6, R94.1
unnamed: JP7.3, R91.2
unnamed: JP8.5, R93.1
unnamed: JP7.4, R92.2
unnamed: JP7.5, R93.2
unnamed: JP8.4, R92.1
unnamed: JP8.3, R91.1
unnamed: JP7.6, R94.2
unnamed: JP7.7, R95.2
unnamed: JP8.2, R90.1
unnamed: JP8.1, R89.1
unnamed: JP7.8, R96.2
unnamed: JP9.1, R97.2
unnamed: JP10.8, R104.1
unnamed: JP10.7, R103.1
unnamed: JP9.2, R98.2
unnamed: JP10.6, R102.1
unnamed: JP9.3, R99.2
unnamed: JP10.5, R101.1
unnamed: JP9.4, R100.2
unnamed: JP9.5, R101.2
unnamed: JP10.4, R100.1
unnamed: JP10.3, R99.1
unnamed: JP9.6, R102.2
unnamed: JP9.7, R103.2
unnamed: JP10.2, R98.1
unnamed: JP10.1, R97.1
unnamed: JP9.8, R104.2
READ_BRAKE: U$18.3, U$23.6, U$23.7
READ_BRAKE1: U$39.3, U$46.6, U$46.7
READ_CHARGE: BSPD1:U$12.1, BSPD1:U$12.2, LED2.A, U$16.P$1, U$18.6
READ_CHARGE1: BSPD1:U$8.1, BSPD1:U$8.2, LED11.A, U$37.P$1, U$39.6
READ_FAULT: BSPD1:U$12.6, BSPD1:U$12.7, LED3.A, POWER.5, U$15.P$1, U$18.7, X5.5
READ_FAULT1: BSPD1:U$8.6, BSPD1:U$8.7, LED12.A, POWER1.5, U$36.P$1, U$39.7, X11.5
READ_SWITCH: BSPD1:U$6.4, LED1.A, POWER.6, U$17.P$1, U$18.5, X5.6
READ_SWITCH1: BSPD1:U$20.4, LED10.A, POWER1.6, U$38.P$1, U$39.5, X11.6
READ_UPSTREAM_SHUTDOWN: U$18.4, U$23.1, U$23.2
READ_UPSTREAM_SHUTDOWN1: U$39.4, U$46.1, U$46.2
SCK: PI_ODD.12, U$11.13
SCK1: PI_ODD1.12, U$32.13
SCK_TEENSY: U$1.D13, U$18.13
SCK_TEENSY1: U$24.D13, U$39.13
SCL: ADXL345_BREAKOUT.8, R31.1, U$1.A5
SCL1: ADXL345_BREAKOUT1.8, R63.1, U$24.A5
SDA: ADXL345_BREAKOUT.7, R32.1, U$1.A4
SDA1: ADXL345_BREAKOUT1.7, R64.1, U$24.A4
SHUTDOWN_A: POWER.1, R13.2, SOFTWARE_SHUTOFF.P, X5.1
SHUTDOWN_A1: POWER1.1, R38.2, SOFTWARE_SHUTOFF1.P, X11.1
SHUTDOWN_B: BSPD1:U$1.P, R29.1, SOFTWARE_SHUTOFF.S
SHUTDOWN_B1: BSPD1:U$16.P, R60.1, SOFTWARE_SHUTOFF1.S
SHUTDOWN_D: BSPD1:U$3.7, POWER.2, X5.2
SHUTDOWN_D1: BSPD1:U$14.7, POWER1.2, X11.2
SHUTDOWN_RELAY_CTRL: U$1.A2, U$5.1
SHUTDOWN_RELAY_CTRL1: U$24.A2, U$26.1
SIGNAL_ACCEL1: PEDALS.9, R9.1, R11.1, U$18.1, X4.9
SIGNAL_ACCEL2: PEDALS.6, R10.1, R30.1, U$18.2, X4.6
SIGNAL_ACCEL3: PEDALS1.6, R57.1, R62.1, U$39.2, X10.6
SIGNAL_ACCEL4: PEDALS1.9, R58.1, R61.1, U$39.1, X10.9
SIGNAL_BRAKE: BSPD1:R4.2, BSPD1:U$10.5, PEDALS.3, POWER.4, U$13.P$1, U$23.5, X4.3, X5.4
SIGNAL_BRAKE1: BSPD1:R13.2, BSPD1:U$7.5, PEDALS1.3, POWER1.4, U$34.P$1, U$46.5, X10.3, X11.4
SIGNAL_CURRENT: BSPD1:R7.1, BSPD1:U$10.3, POWER.3, U$14.P$1, X5.3
SIGNAL_CURRENT1: BSPD1:R14.1, BSPD1:U$7.3, POWER1.3, U$35.P$1, X11.3
THERM1: JP1.2, R65.2, U$47.A9
THERM2: JP1.3, R70.2, U$47.A10
THERM3: JP1.4, R71.2, U$47.A11
THERM4: JP2.2, R72.2, U$47.A6
THERM5: JP2.3, R73.2, U$47.A7
THERM6: JP3.2, R74.2, U$47.A3
THERM9: JP4.2, R77.2, U$47.A0
THERM10: JP4.3, R66.2, U$47.A1
TS_GND: JP6.2, R65.1, R66.1, R68.1, R69.1, R70.1, R71.1, R72.1, R73.1, R74.1, R75.1, R76.1, R77.1

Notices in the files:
parts and their libraries:
SparkFun-FreqCtrl: Licensing: Creative Commons ShareAlike 4.0 International - https://creativecommons.org/licenses/by-sa/4.0
